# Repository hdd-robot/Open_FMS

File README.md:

# Open_FMS
Open fleet management system

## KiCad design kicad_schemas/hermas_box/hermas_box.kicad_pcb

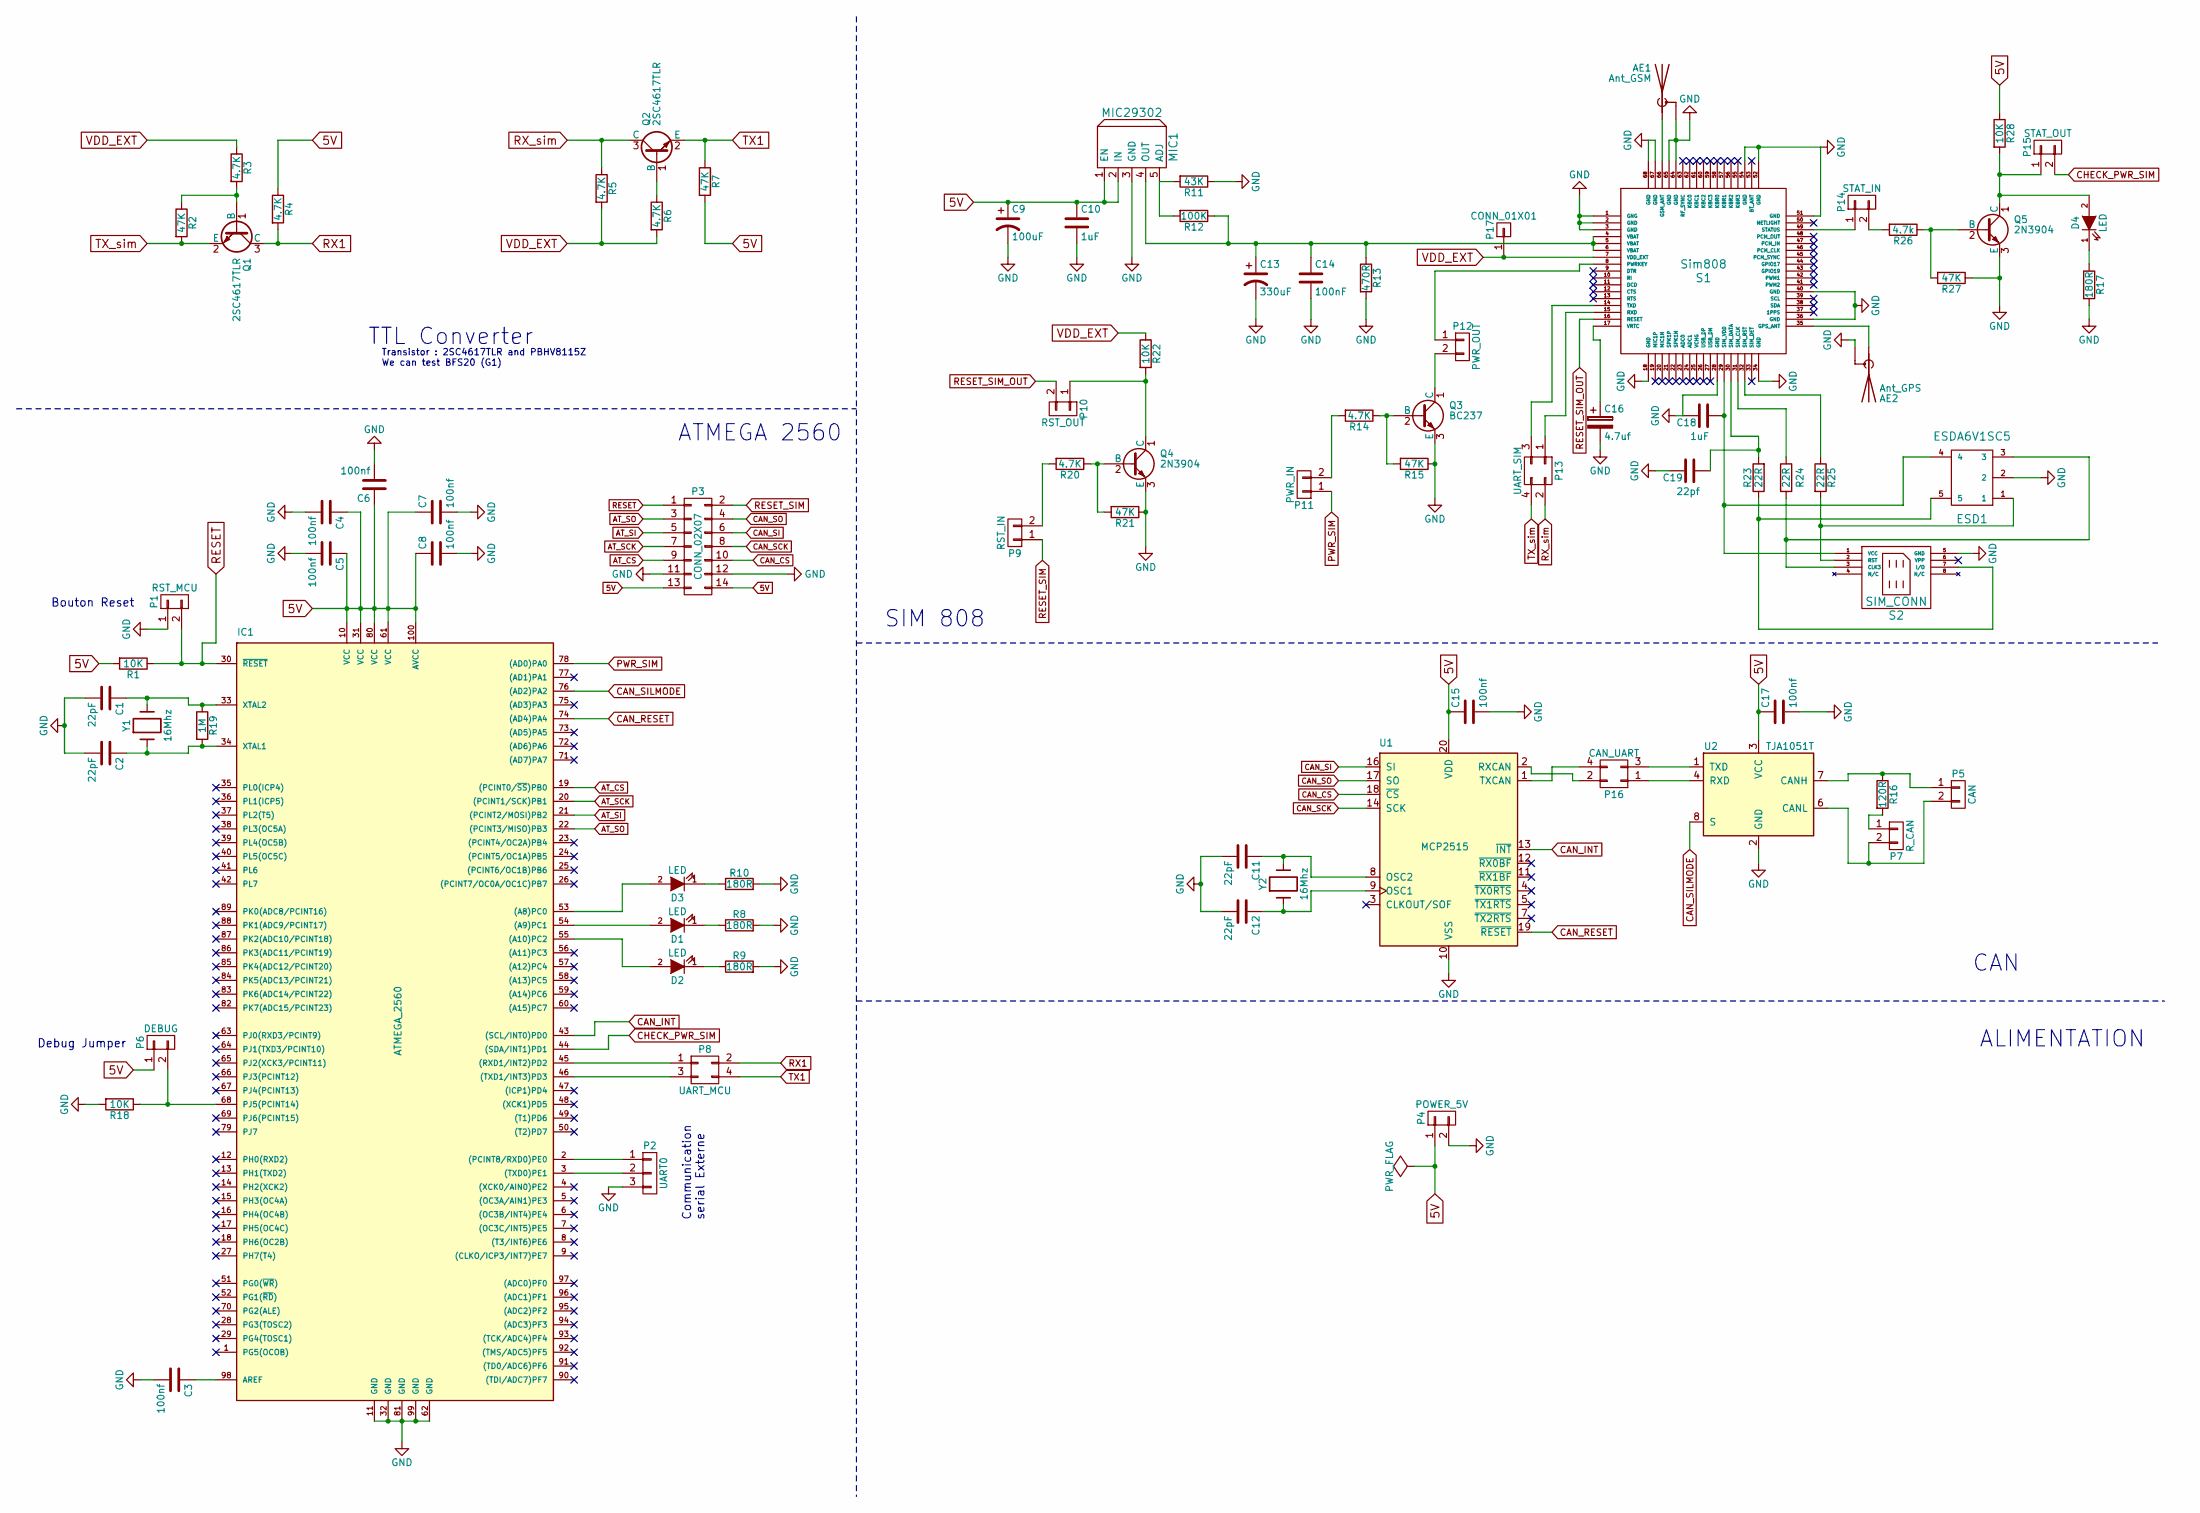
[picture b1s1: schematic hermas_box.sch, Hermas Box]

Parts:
AE1: Ant_GSM; SMA-13
AE2: Ant_GPS; SMA-13
C1, C2, C11, C12: 22pF; C_1206
C3, C4, C5, C6, C7, C8, C15, C17: 100nf; C_1206
C9: 100uF; c_elec_8x5.4
C10, C18: 1uF; C_1206
C13: 330uF; c_elec_10x10
C14: 100nF; C_1206
C16: 4.7uf; c_elec_4x5.3
C19: 22pf; C_1206
D1, D2, D3, D4: LED; LED_1206
ESD1: ESDA6V1SC5; SOT-23-5
IC1: ATMEGA_2560; LQFP-100_14x14mm_Pitch0.5mm
MIC1: MIC29302; TO-263-5Lead
P1: RST_MCU; Pin_Header_Straight_1x02
P2: UART0; Pin_Header_Straight_1x03
P3: CONN_02X07; Pin_Header_Straight_2x07
P4: POWER_5V; Pin_Header_Straight_1x02
P5: CAN; Pin_Header_Straight_1x02
P6: DEBUG; Pin_Header_Straight_1x02
P7: R_CAN; Pin_Header_Straight_1x02
P8: UART_MCU; Pin_Header_Straight_2x02
P9: RST_IN; Pin_Header_Straight_1x02
P10: RST_OUT; Pin_Header_Straight_1x02
P11: PWR_IN; Pin_Header_Straight_1x02
P12: PWR_OUT; Pin_Header_Straight_1x02
P13: UART_SIM; Pin_Header_Straight_2x02
P14: STAT_IN; Pin_Header_Straight_1x02
P15: STAT_OUT; Pin_Header_Straight_1x02
P16: CAN_UART; Pin_Header_Straight_2x02
P17: CONN_01X01; Pin_Header_Straight_1x01
Q1, Q2: 2SC4617TLR; SOT-23
Q3: BC237; SOT-23
Q4, Q5: 2N3904; SOT-23
R1, R18, R22, R28: 10K; R_1206
R2, R7, R15, R21, R27: 47K; R_1206
R3, R4, R5, R6, R14, R20: 4.7K; R_1206
R8, R9, R10, R17: 180R; R_1206
R11: 43K; R_1206
R12: 100K; R_1206
R13: 470R; R_1206
R16: 120R; R_1206
R19: 1M; R_1206
R23, R24, R25: 22R; R_1206
R26: 4.7k; R_1206
S1: Sim808; SIM808
S2: SIM_CONN; SIM_CONNECTOR
U1: MCP2515; TSSOP-20_4.4x6.5mm_Pitch0.65mm
U2: TJA1051T; SOIC-8_3.9x4.9mm_Pitch1.27mm
Y1, Y2: 16Mhz; Crystal_HC49-SD_SMD

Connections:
5V: C4.1, C5.1, C6.1, C7.1, C8.1, C9.1, C10.1, C15.1, C17.1, IC1.10 (VCC), IC1.31 (VCC), IC1.61 (VCC), IC1.80 (VCC), IC1.100 (AVCC), MIC1.1 (EN), MIC1.2 (IN), P3.13, P3.14, P4.1, P6.1, R1.2, R4.1, R7.2, R28.1, U1.20 (VDD), U2.3 (VCC)
AT_CS: IC1.19 ((PCINT0/~SS~)PB0), P3.9
AT_SCK: IC1.20 ((PCINT1/SCK)PB1), P3.7
AT_SI: IC1.21 ((PCINT2/MOSI)PB2), P3.5
AT_SO: IC1.22 ((PCINT3/MISO)PB3), P3.3
CAN_CS: P3.10, U1.18 (~CS)
CAN_INT: IC1.43 ((SCL/INT0)PD0), U1.13 (~INT)
CAN_RESET: IC1.74 ((AD4)PA4), U1.19 (~RESET)
CAN_SCK: P3.8, U1.14 (SCK)
CAN_SI: P3.6, U1.16 (SI)
CAN_SILMODE: IC1.76 ((AD2)PA2), U2.8 (S)
CAN_SO: P3.4, U1.17 (SO)
CHECK_PWR_SIM: IC1.44 ((SDA/INT1)PD1), P15.2
GND: AE1.2 (Shield), AE2.2 (Shield), C1.2, C2.2, C3.2, C4.2, C5.2, C6.2, C7.2, C8.2, C9.2, C10.2, C11.2, C12.2, C13.2, C14.2, C15.2, C16.2, C17.2, C18.2, C19.2, ESD1.2, IC1.11 (GND), IC1.32 (GND), IC1.62 (GND), IC1.81 (GND), IC1.99 (GND), MIC1.3 (GND), P1.1, P2.3, P3.11, P3.12, P4.2, Q3.3 (E), Q4.3 (E), Q5.3 (E), R8.2, R9.2, R10.2, R11.1, R13.2, R15.1, R17.2, R18.2, R21.1, R27.1, S1.1 (GNG), S1.2 (GND), S1.3 (GND), S1.18 (GND), S1.28 (GND), S1.34 (GND), S1.36 (GND), S1.40 (GND), S1.51 (GND), S1.52 (GND), S1.54 (GND), S1.64 (GND), S1.65 (GND), S1.67 (GND), S1.68 (GND), S2.5 (GND), U1.10 (VSS), U2.2 (GND)
unnamed: AE1.1 (A), S1.66 (GSM_ANT)
unnamed: AE2.1 (A), S1.35 (GPS_ANT)
unnamed: C1.1, IC1.33 (XTAL2), R19.1, Y1.2
unnamed: C2.1, IC1.34 (XTAL1), R19.2, Y1.1
unnamed: C3.1, IC1.98 (AREF)
unnamed: C11.1, U1.8 (OSC2), Y2.2
unnamed: C12.1, U1.9 (OSC1), Y2.1
unnamed: C13.1, C14.1, MIC1.4 (OUT), R12.1, R13.1, S1.4 (VBAT), S1.5 (VBAT), S1.6 (VBAT)
unnamed: C16.1, S1.17 (VRTC)
unnamed: C18.1, ESD1.4, S1.29 (SIM_VDD), S2.1 (VCC)
unnamed: C19.1, R23.2, S1.30 (SIM_DATA)
unnamed: D1.1 (K), R8.1
unnamed: D1.2 (A), IC1.54 ((A9)PC1)
unnamed: D2.1 (K), R9.1
unnamed: D2.2 (A), IC1.55 ((A10)PC2)
unnamed: D3.1 (K), R10.1
unnamed: D3.2 (A), IC1.53 ((A8)PC0)
unnamed: D4.1 (K), R17.1
unnamed: D4.2 (A), P15.1, Q5.1 (C), R28.2
unnamed: ESD1.1, R25.2, S2.2 (RST)
unnamed: ESD1.3, R24.2, S2.3 (CLK3)
unnamed: ESD1.5, R23.1, S2.7 (I/O)
unnamed: IC1.2 ((PCINT8/RXD0)PE0), P2.1
unnamed: IC1.3 ((TXD0)PE1), P2.2
unnamed: IC1.45 ((RXD1/INT2)PD2), P8.1
unnamed: IC1.46 ((TXD1/INT3)PD3), P8.3
unnamed: IC1.68 (PJ5(PCINT14)), P6.2, R18.1
unnamed: MIC1.5 (ADJ), R11.2, R12.2
unnamed: P5.1, R16.1, U2.7 (CANH)
unnamed: P5.2, P7.2, U2.6 (CANL)
unnamed: P7.1, R16.2
unnamed: P9.2, R20.2
unnamed: P10.1, Q4.1 (C), R22.2
unnamed: P11.2, R14.2
unnamed: P12.1, S1.8 (PWRKEY)
unnamed: P12.2, Q3.1 (C)
unnamed: P13.1, S1.15 (RXD)
unnamed: P13.3, S1.14 (TXD)
unnamed: P14.1, S1.49 (STATUS)
unnamed: P14.2, R26.2
unnamed: P16.1, U2.4 (RXD)
unnamed: P16.2, U1.2 (RXCAN)
unnamed: P16.3, U2.1 (TXD)
unnamed: P16.4, U1.1 (TXCAN)
unnamed: Q1.1 (B), R2.1, R3.2
unnamed: Q2.1 (B), R6.1
unnamed: Q3.2 (B), R14.1, R15.2
unnamed: Q4.2 (B), R20.1, R21.2
unnamed: Q5.2 (B), R26.1, R27.2
unnamed: R24.1, S1.31 (SIM_CLK)
unnamed: R25.1, S1.32 (SIM_RST)
PWR_SIM: IC1.78 ((AD0)PA0), P11.1
RESET: IC1.30 (~RESET), P1.2, P3.1, R1.1
RESET_SIM: P3.2, P9.1
RESET_SIM_OUT: P10.2, S1.16 (RESET)
RX1: P8.2, Q1.3 (C), R4.2
RX_sim: P13.2, Q2.3 (C), R5.1
TX1: P8.4, Q2.2 (E), R7.1
TX_sim: P13.4, Q1.2 (E), R2.2
VDD_EXT: P17.1, R3.1, R5.2, R6.2, R22.1, S1.7 (VDD_EXT)

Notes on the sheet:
TTL Converter
ATMEGA 2560
SIM 808
ALIMENTATION
CAN
Transistor : 2SC4617TLR and PBHV8115Z We can test BFS20 (G1)
Communication serial Externe
Bouton Reset
Debug Jumper

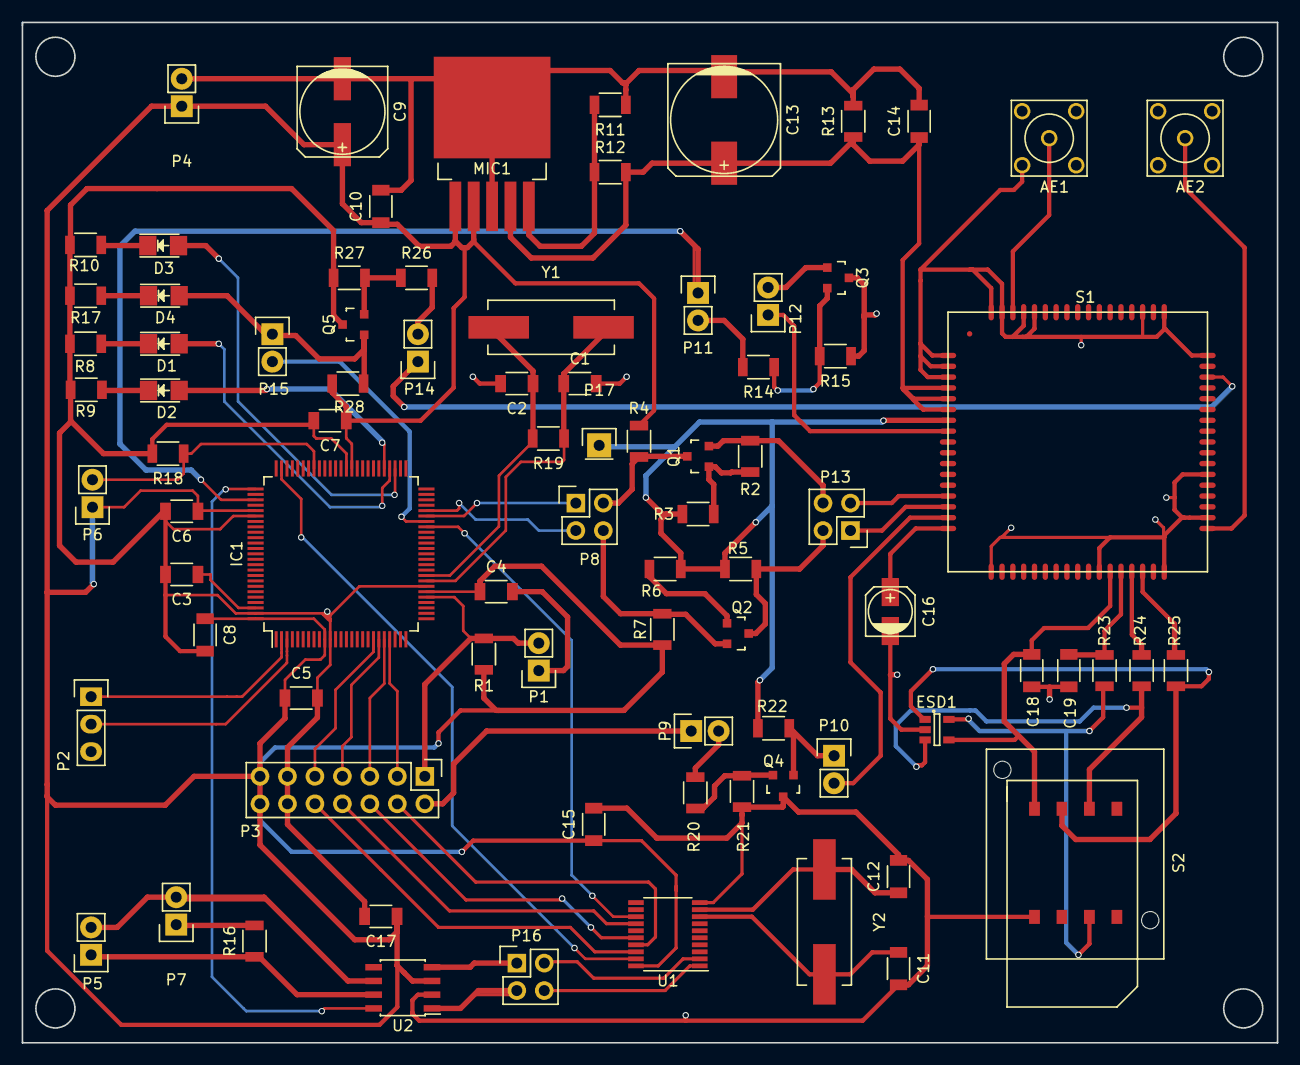
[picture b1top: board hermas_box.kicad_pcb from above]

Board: 2 copper layers, 116.1 x 94.4 mm, 84 parts (0 on the bottom side), 74 nets.

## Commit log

2021-11-15 Wab_application
2021-11-15 kicad
